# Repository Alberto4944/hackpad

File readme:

This is a 5 key hackpad with an oled screen and a rotary encoder. Was really fun to learn and make.

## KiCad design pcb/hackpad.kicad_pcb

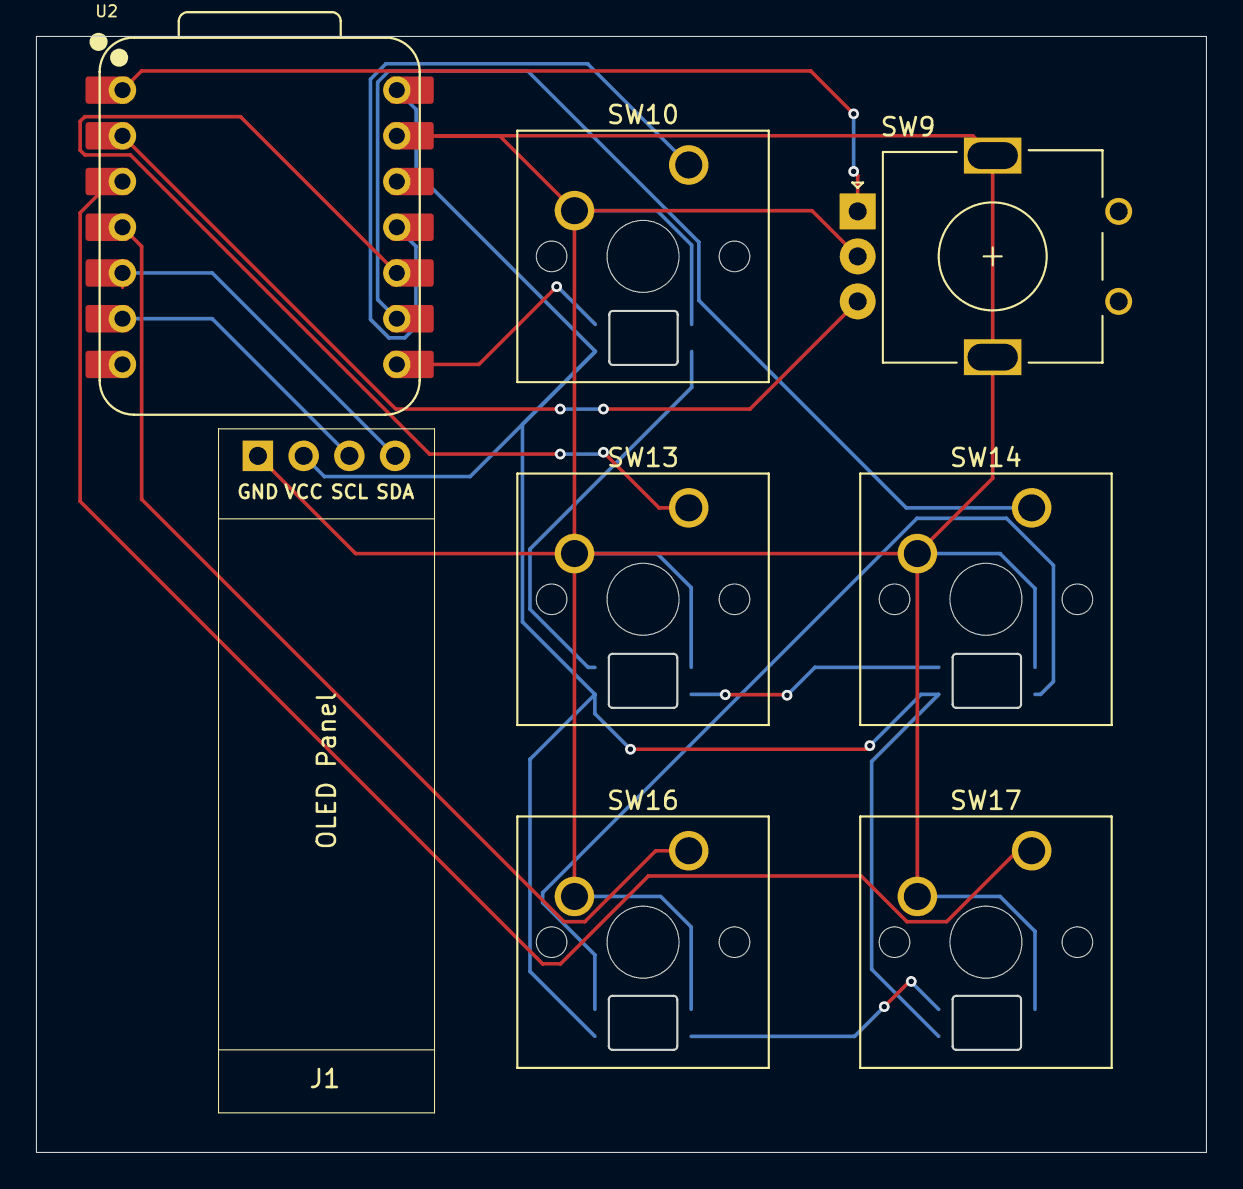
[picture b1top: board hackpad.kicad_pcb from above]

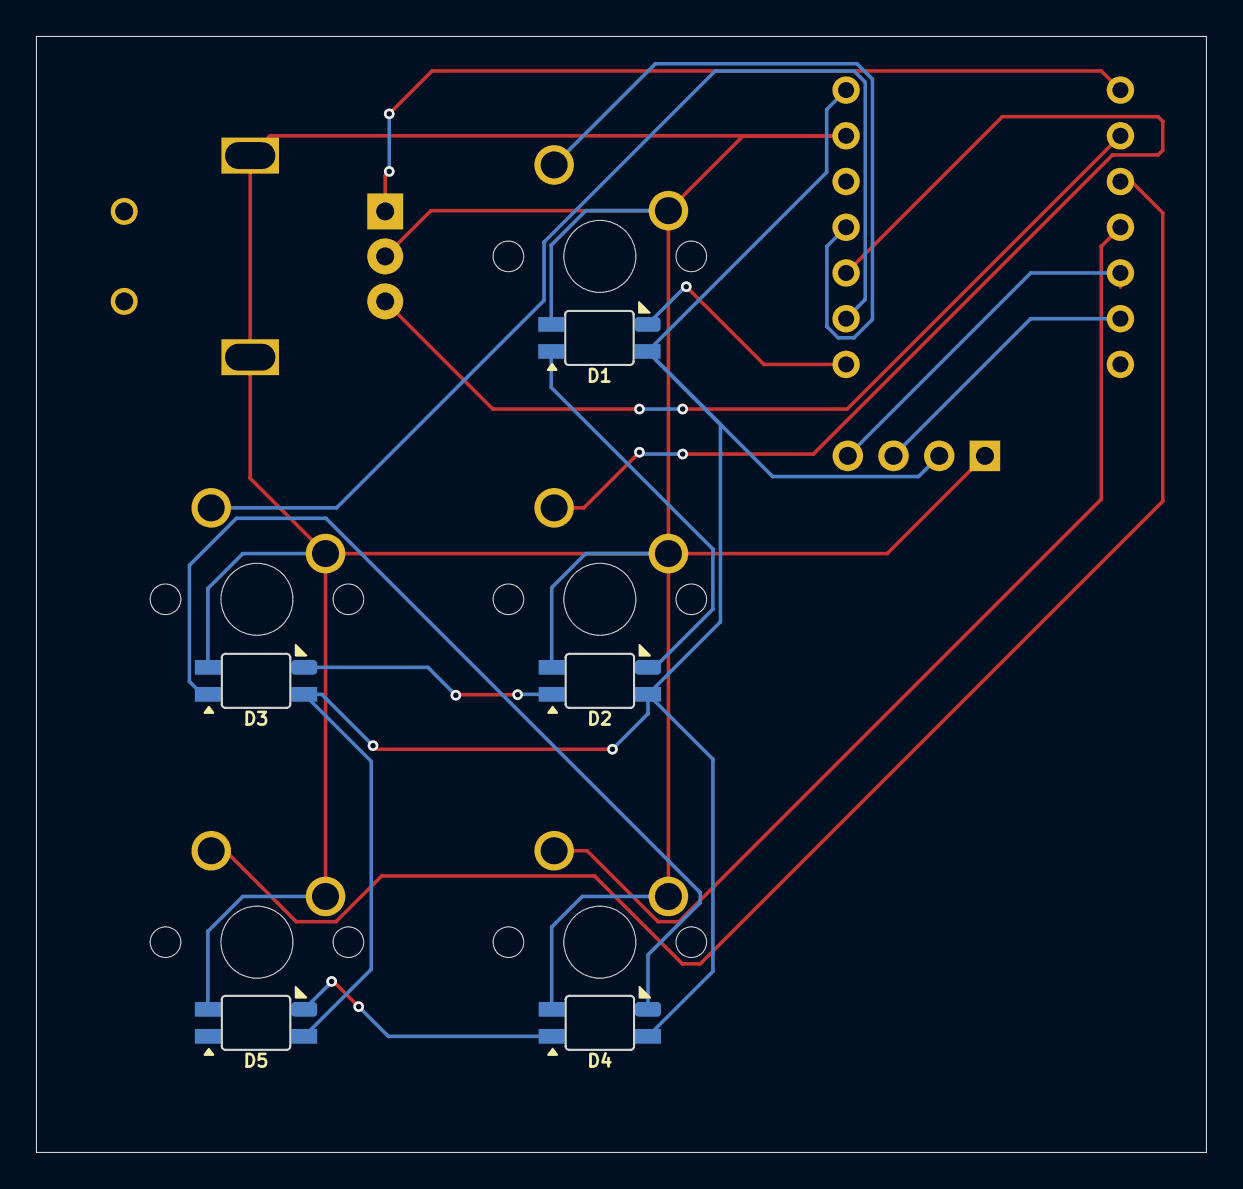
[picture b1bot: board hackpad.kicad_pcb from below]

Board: 2 copper layers, 64.9 x 61.9 mm, 13 parts (5 on the bottom side), 16 nets.

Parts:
D1, D2, D3, D4, D5: SK6812MINI; SK6812-MINI-E
J1: OLED_128x32; SSD1306-0.91-OLED-4pin-128x32
SW9: RotaryEncoder_Switch_MP; RotaryEncoder_Alps_EC11E_Vertical_H20mm
SW10, SW13, SW14, SW16, SW17: SW_Push_45deg; SW_Cherry_MX_1.00u_PCB
U2: XIAO-RP2040-DIP

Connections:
+5V: D1.4 (VDD), D2.4 (VDD), D3.4 (VDD), D4.4 (VDD), D5.4 (VDD), J1.2 (VCC), U2.14 (VBUS)
GND: D1.2 (VSS), D2.2 (VSS), D3.2 (VSS), D4.2 (VSS), D5.2 (VSS), J1.1 (GND), SW9.C, SW9.MP, SW10.2, SW13.2, SW14.2, SW16.2, SW17.2, U2.13 (GND)
unnamed: D1.1 (DOUT), D2.3 (DIN)
unnamed: D2.1 (DOUT), D3.3 (DIN)
unnamed: D3.1 (DOUT), D4.3 (DIN)
unnamed: D4.1 (DOUT), D5.3 (DIN)
unnamed: SW14.1, U2.9 (GPIO2/SCK)
unnamed: SW10.1, U2.11 (GPIO3/MOSI)
unnamed: SW13.1, U2.10 (GPIO4/MISO)
unnamed: SW17.1, U2.3 (GPIO28/ADC2/A2)
unnamed: SW16.1, U2.4 (GPIO29/ADC3/A3)
POT_ANALOG_1: SW9.A, U2.1 (GPIO26/ADC0/A0)
POT_ANALOG_2: SW9.B, U2.2 (GPIO27/ADC1/A1)
SCL: J1.3 (SCL), U2.6 (GPIO7/SCL)
SDA: J1.4 (SDA), U2.5 (GPIO6/SDA)
SK6812MINI: D1.3 (DIN), U2.8 (GPIO1/RX)

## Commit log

2025-08-01 first
